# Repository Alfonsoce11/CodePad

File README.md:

# CodePad
A simple 9 key macropad that has shortcuts for coding.
| | |
|-|-|
|  |  |

## Shortcuts
* CMD+S - Save
* CMD+P - Quick Open
* CMD+Shift+P - Command Palette
* CMD+/ - Toggle comment
* CMD+J - Opens terminal
* CMD+N - New file
* CMD+] - Indent
* CMD+B - Toggle sidebar
* CMD+Shift+O - Go to symbol

I made the firmware using KMK

## PCB
| Schematic | PCB | 3D PCB |
|-----------|-----|--------|
|  |  |  |

I made the PCB in KiCad

## Case
The case only has two parts, the top and the bottom which can be connected with 4 screws.
| Top | Bottom | Assembled Case |
|-----|--------|----------------|
| |  |  |

I made the case on OnShape

## BOM
* 1x XIAO RP2040
* 9x Cherry MX Switches
* 9x DSA Keycaps
* 4x M3x16 Bolt
* 4x M3 Heatset

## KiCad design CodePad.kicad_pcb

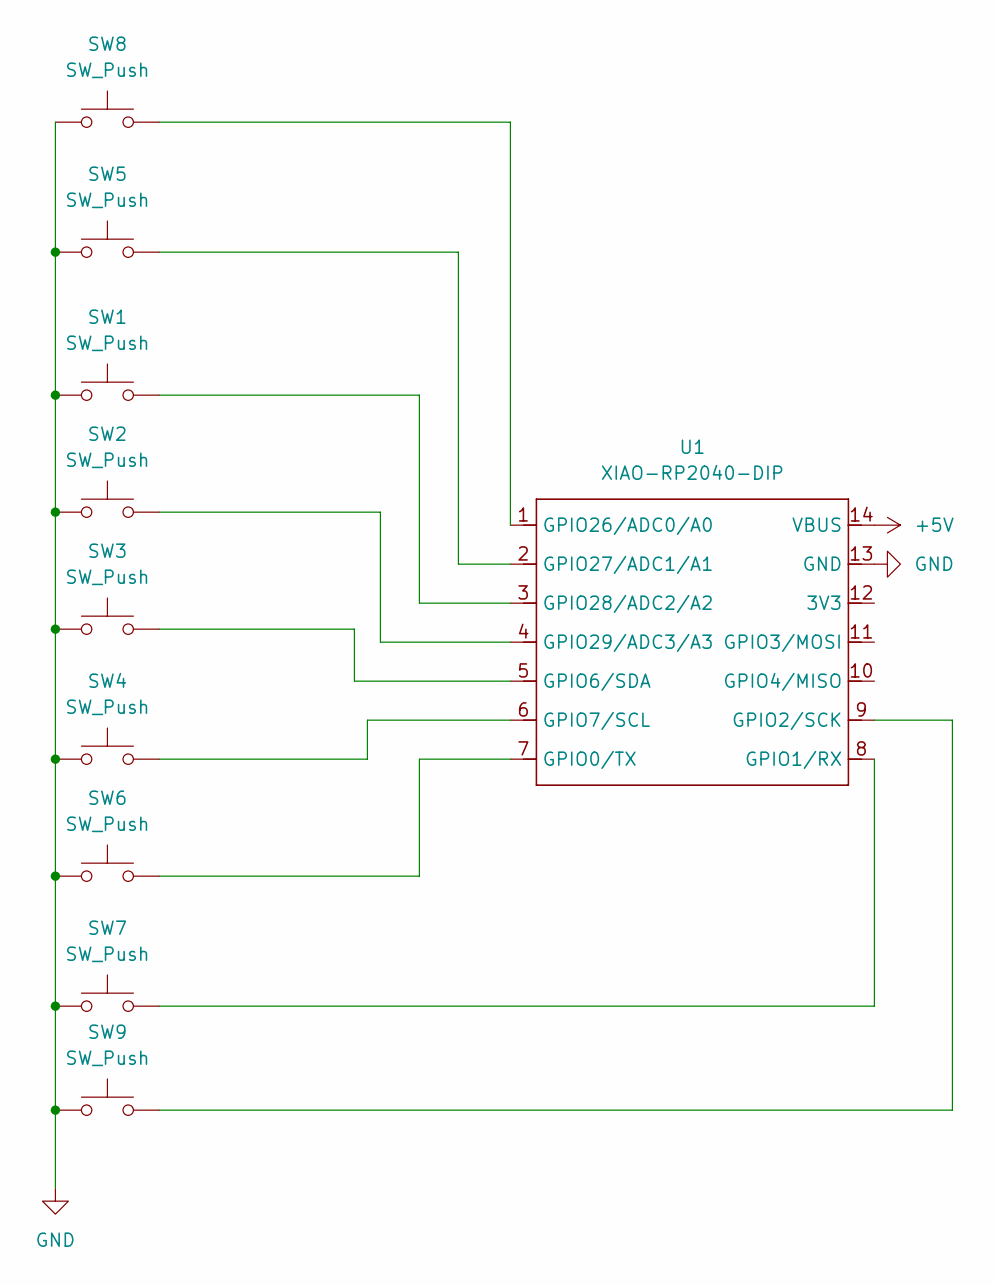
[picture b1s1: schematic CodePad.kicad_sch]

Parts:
SW1, SW2, SW3, SW4, SW5, SW6, SW7, SW8, SW9: SW_Push; SW_Cherry_MX_1.00u_PCB
U1: XIAO-RP2040-DIP

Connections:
+5V: U1.14 (VBUS)
GND: SW1.1, SW2.1, SW3.1, SW4.1, SW5.1, SW6.1, SW7.1, SW8.1, SW9.1, U1.13 (GND)
unnamed: SW6.2, U1.7 (GPIO0/TX)
unnamed: SW7.2, U1.8 (GPIO1/RX)
unnamed: SW9.2, U1.9 (GPIO2/SCK)
unnamed: SW3.2, U1.5 (GPIO6/SDA)
unnamed: SW4.2, U1.6 (GPIO7/SCL)
unnamed: SW8.2, U1.1 (GPIO26/ADC0/A0)
unnamed: SW5.2, U1.2 (GPIO27/ADC1/A1)
unnamed: SW1.2, U1.3 (GPIO28/ADC2/A2)
unnamed: SW2.2, U1.4 (GPIO29/ADC3/A3)

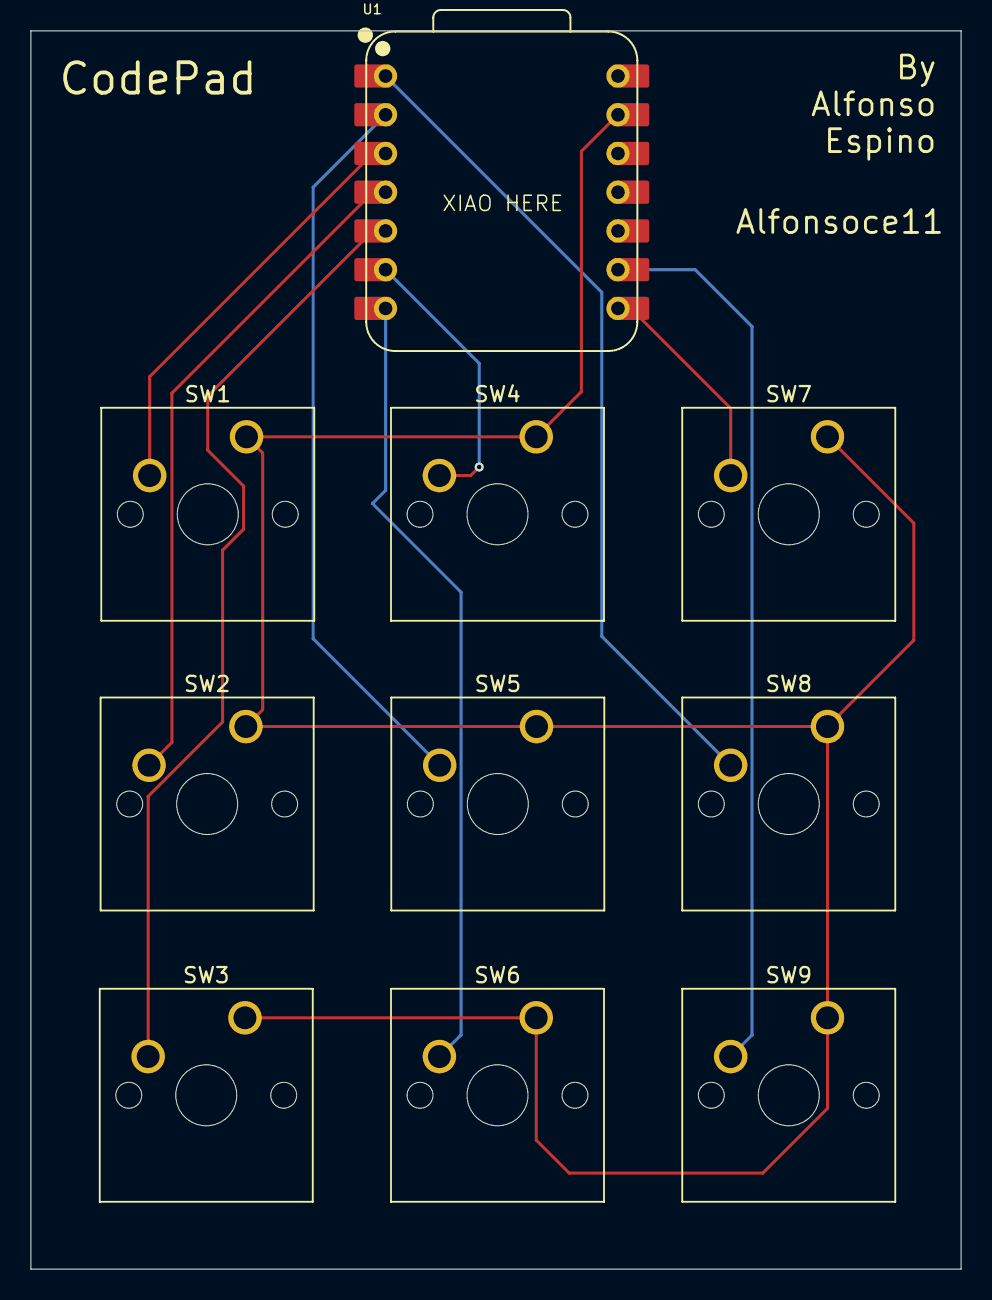
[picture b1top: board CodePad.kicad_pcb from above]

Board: 2 copper layers, 61.0 x 81.2 mm, 10 parts (0 on the bottom side), 10 nets.

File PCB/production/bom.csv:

Designator,Footprint,Quantity,Value,LCSC Part #
"SW1, SW2, SW3, SW4, SW5, SW6, SW7, SW8, SW9",SW_Cherry_MX_1.00u_PCB,9,SW_Push,
U1,XIAO-RP2040-DIP,1,XIAO-RP2040-DIP,

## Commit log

2025-06-16 Rename CodePad.step to CAD/CodePad.step
2025-06-16 Update LICENSE
2025-06-16 delate file
2025-06-16 Create production
2025-06-16 Rename CodePad.kicad_sch to PCB/CodePad.kicad_sch
2025-06-16 Rename PCB/file
2025-06-16 move files
2025-06-16 Added production files
